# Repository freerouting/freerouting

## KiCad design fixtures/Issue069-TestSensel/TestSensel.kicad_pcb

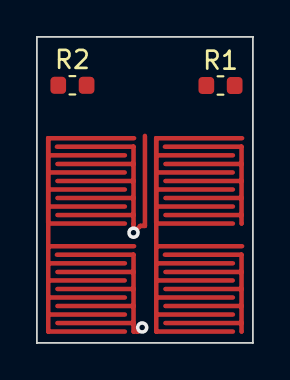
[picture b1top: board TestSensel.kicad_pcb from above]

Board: 2 copper layers, 12.0 x 17.0 mm, 6 parts (0 on the bottom side), 4 nets.

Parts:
J1, J2, J3, J4: Conn_01x02_Male; PCB_Fork_10mils_5mmx5mm
R1, R2: R_Small_US; R_0603_1608Metric

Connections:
/Col_1: J1.2, J2.2, R1.2
/Col_2: J3.2, J4.2, R1.1
/Row_1: J1.1, J3.1, R2.2
/Row_2: J2.1, J4.1, R2.1

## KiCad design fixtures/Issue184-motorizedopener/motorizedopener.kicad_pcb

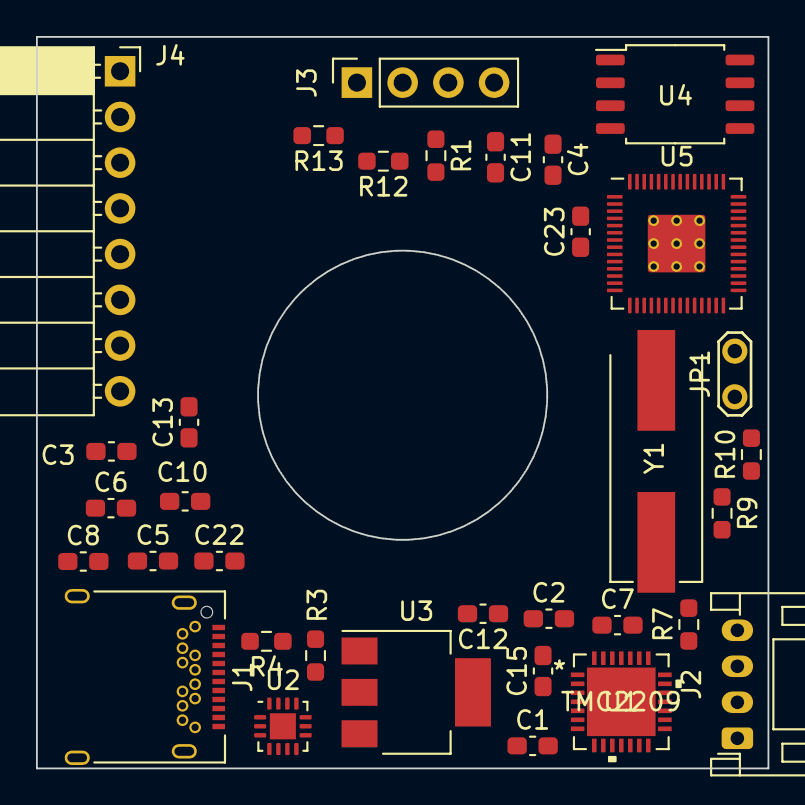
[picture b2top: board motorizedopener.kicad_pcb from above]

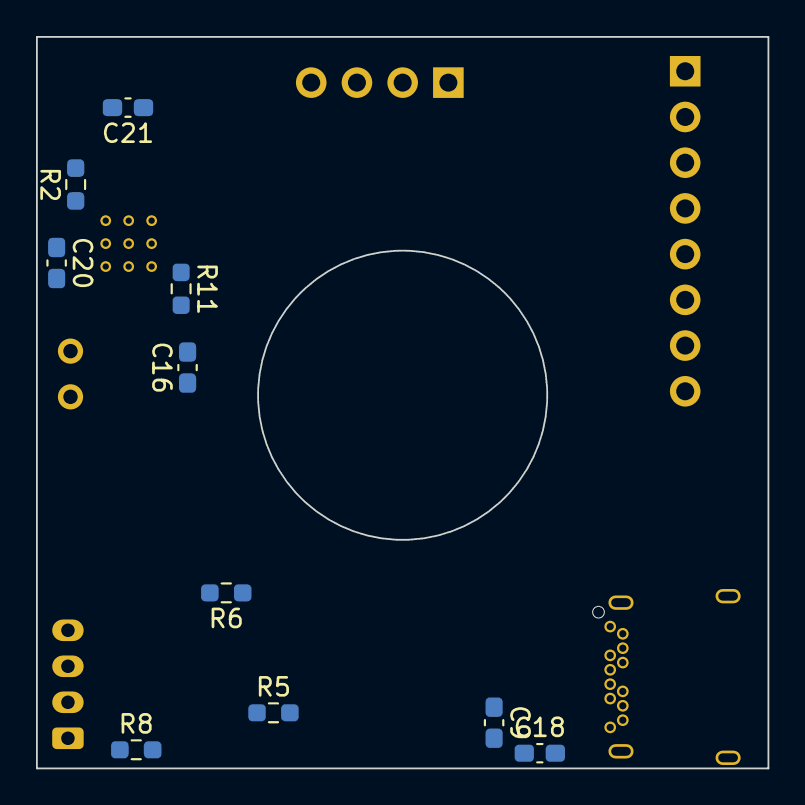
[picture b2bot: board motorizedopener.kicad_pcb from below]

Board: 2 copper layers, 40.6 x 40.6 mm, 44 parts (10 on the bottom side), 49 nets, no tracks yet.

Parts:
C1: 2.2uF; C_0603_1608Metric_Pad1.08x0.95mm_HandSolder
C2, C12: 22nF; C_0603_1608Metric_Pad1.08x0.95mm_HandSolder
C3, C21, C22: 1uF; C_0603_1608Metric_Pad1.08x0.95mm_HandSolder
C4, C6: 0.1uF; C_0603_1608Metric_Pad1.08x0.95mm_HandSolder
C5, C7, C11: 10uF; C_0603_1608Metric_Pad1.08x0.95mm_HandSolder
C8, C9: 470pF; C_0603_1608Metric_Pad1.08x0.95mm_HandSolder
C10, C18: 100nF; C_0603_1608Metric_Pad1.08x0.95mm_HandSolder
C13: 300nF; C_0603_1608Metric_Pad1.08x0.95mm_HandSolder
C15, C16: 27pF; C_0603_1608Metric_Pad1.08x0.95mm_HandSolder
C20: 200nF; C_0603_1608Metric_Pad1.08x0.95mm_HandSolder
C23: 700nF; C_0603_1608Metric_Pad1.08x0.95mm_HandSolder
J1: USB_C_Receptacle; USB_C_Receptacle_Amphenol_12401548E4-2A
J2: Stepper OUT; JST_PH_S4B-PH-K_1x04_P2.00mm_Horizontal
J3: I2C OLED; PinSocket_1x04_P2.54mm_Vertical
J4: SPI RFID; PinSocket_1x08_P2.54mm_Horizontal
JP1: Jumper_2_Open; TestPoint_2Pads_Pitch2.54mm_Drill0.8mm
R1, R7: 10k; R_0603_1608Metric_Pad0.98x0.95mm_HandSolder
R2, R3, R4: 4.7k; R_0603_1608Metric_Pad0.98x0.95mm_HandSolder
R5, R6: 220m; R_0603_1608Metric_Pad0.98x0.95mm_HandSolder
R8: 4.4k; R_0603_1608Metric_Pad0.98x0.95mm_HandSolder
R9, R10, R11: 1k; R_0603_1608Metric_Pad0.98x0.95mm_HandSolder
R12, R13: 27.4; R_0603_1608Metric_Pad0.98x0.95mm_HandSolder
U1: TMC2209
U2: FUSB302B01MPX; WQFN-14-1EP_2.5x2.5mm_P0.5mm_EP1.45x1.45mm
U3: NCP1117-3.3_SOT223; SOT-223-3_TabPin2
U4: W25Q128JVS; SOIC-8_5.23x5.23mm_P1.27mm
U5: RP2040; RP2040-QFN-56
Y1: 12.000MHZ; Crystal_SMD_HC49-US

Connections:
+1V1: C20.1, C21.2, U5.23 (DVDD), U5.45 (VREG_VOUT), U5.50 (DVDD)
+3V3: C3.2, C4.2, C10.1, C11.1, C18.1, C22.2, C23.1, J3.2, J4.1, R2.2, R3.2, R4.2, R7.2, U1.15 (VCC_IO), U2.3 (VDD), U2.4 (VDD), U3.2 (VO), U4.8 (VCC), U5.1 (IOVDD), U5.10 (IOVDD), U5.22 (IOVDD), U5.33 (IOVDD), U5.42 (IOVDD), U5.43 (ADC_AVDD), U5.44 (VREG_IN), U5.48 (USB_VDD), U5.49 (IOVDD)
GND: C1.2, C3.1, C4.1, C5.2, C6.2, C7.2, C8.2, C9.2, C10.2, C11.2, C13.2, C15.1, C16.1, C18.2, C20.2, C21.1, C22.1, C23.2, J1.A1 (GND), J1.A12 (GND), J1.B1 (GND), J1.B12 (GND), J1.S1 (SHIELD), J3.1, J4.3, JP1.1 (A), R1.1, R5.1, R6.1, R8.1, U1.3 (GND), U1.9 (MS1_AD0), U1.10 (MS2_AD1), U1.13 (CLK), U1.18 (GND), U1.20 (STDBY), U1.29 (GND), U2.8 (GND), U2.9 (GND), U2.15 (GND), U3.1 (GND), U4.4 (GND), U5.19 (TESTEN), U5.57 (GND)
unnamed: C1.1, U1.8 (5VOUT)
unnamed: C2.1, U1.4 (CPO)
unnamed: C2.2, U1.5 (CPI)
unnamed: C5.1, C6.1, U2.12 (VCONN), U2.13 (VCONN)
unnamed: C12.1, U1.6 (VCP)
unnamed: C15.2, U5.20 (XIN), Y1.1
unnamed: C16.2, R10.1, Y1.2
unnamed: J2.1, U1.26 (OB1)
unnamed: J2.2, U1.24 (OA1)
unnamed: J2.3, U1.21 (OA2)
unnamed: J2.4, U1.1 (OB2)
unnamed: J3.3, U5.30 (GPIO19)
unnamed: J3.4, U5.29 (GPIO18)
unnamed: J4.2, U5.9 (GPIO7)
unnamed: J4.4, U5.14 (GPIO11)
unnamed: J4.5, U5.15 (GPIO12)
unnamed: J4.6, U5.13 (GPIO10)
unnamed: J4.7, U5.16 (GPIO13)
unnamed: JP1.2 (B), R9.1
unnamed: R5.2, U1.23 (BRA)
unnamed: R6.2, U1.27 (BRB)
unnamed: R7.1, R8.2, U1.17 (VREF)
unnamed: R9.2, U4.1 (~CS), U5.56 (QSPI_SS)
unnamed: R10.2, U5.21 (XOUT)
unnamed: R11.1, U5.11 (GPIO8)
unnamed: R12.1, U5.47 (USB_DP)
unnamed: R13.1, U5.46 (USB_DM)
unnamed: U4.2 (DO(IO1)), U5.55 (QSPI_SD1)
unnamed: U4.3 (IO2), U5.54 (QSPI_SD2)
unnamed: U4.5 (DI(IO0)), U5.53 (QSPI_SD0)
unnamed: U4.6 (CLK), U5.52 (QSPI_SCLK)
unnamed: U4.7 (IO3), U5.51 (QSPI_SD3)
PWR-INT_N: R4.1, U2.5 (INT_N), U5.31 (GPIO20)
PWR-SCL: R3.1, U2.6 (SCL), U5.28 (GPIO17)
PWR-SDA: R2.1, U2.7 (SDA), U5.27 (GPIO16)
USB-D+: J1.A6 (D+), J1.B6 (D+), R12.2
USB-D-: J1.A7 (D-), J1.B7 (D-), R13.2
VBUS: C7.1, C12.2, C13.1, J1.A4 (VBUS), J1.A9 (VBUS), J1.B4 (VBUS), J1.B9 (VBUS), U1.22 (VS), U1.28 (VS), U2.2 (VBUS), U3.3 (VI)
cc1: C9.1, J1.A5 (CC1), U2.10 (CC1), U2.11 (CC1)
cc2: C8.1, J1.B5 (CC2), U2.1 (CC2), U2.14 (CC2)
tmc_DIAG: U1.11 (DIAG), U5.39 (GPIO27_ADC1)
tmc_DIR: U1.19 (DIR), U5.17 (GPIO14)
tmc_ENN: R1.2, U1.2 (ENN), U5.8 (GPIO6)
tmc_INDEX: U1.12 (INDEX), U5.38 (GPIO26_ADC0)
tmc_STEP: U1.16 (STEP), U5.18 (GPIO15)
tmc_UART: R11.2, U1.14 (PDN_UART), U5.12 (GPIO9)

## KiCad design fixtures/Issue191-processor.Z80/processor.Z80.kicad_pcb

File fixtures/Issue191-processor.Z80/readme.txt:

The processor.Z80 board is the central processor for the duodyne system.  It uses a Z80 8-bit CPU and includes dual-DMA channels.  It supports Interrupt Mode 2 (IM2) and an extended memory mapper.

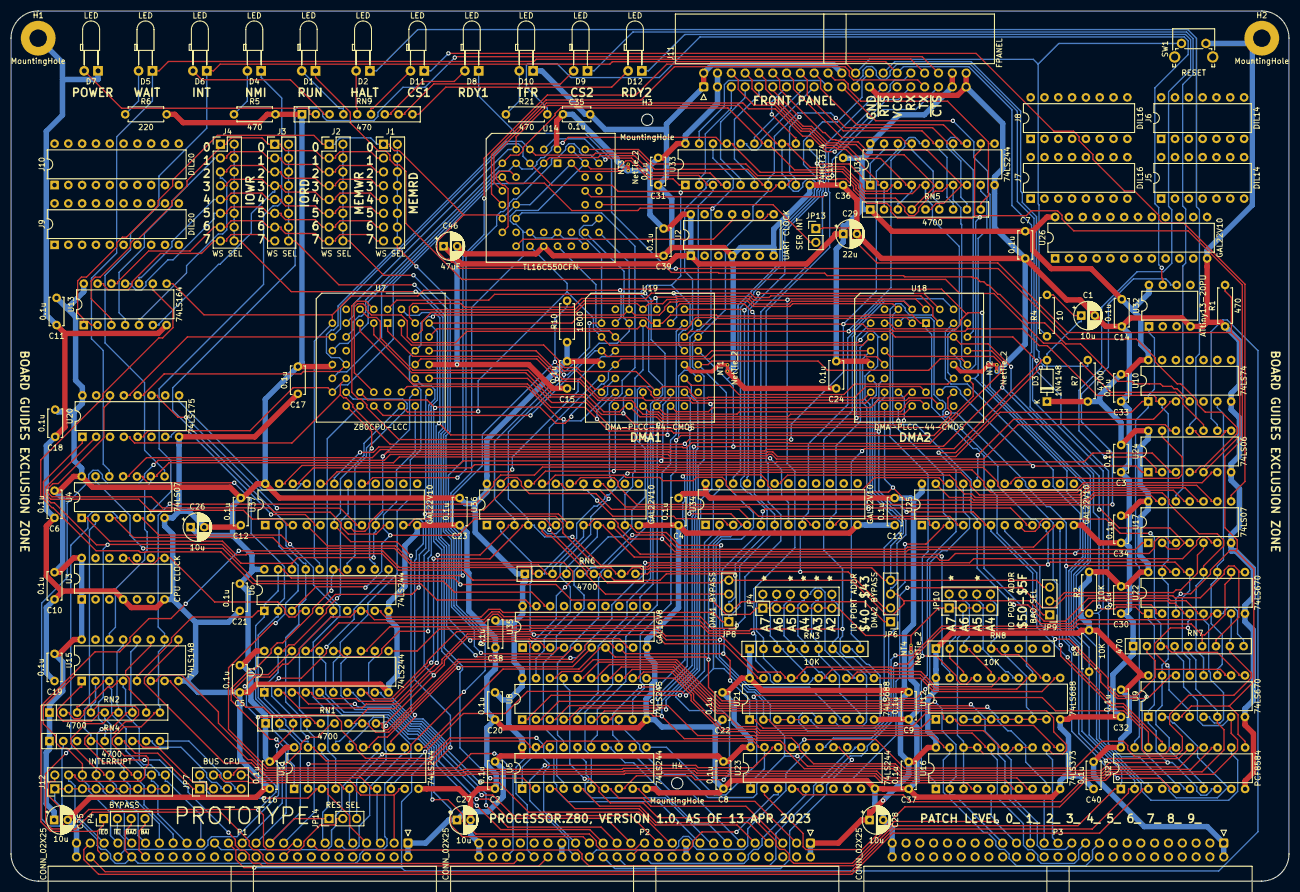
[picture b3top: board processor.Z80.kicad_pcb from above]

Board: 2 copper layers, 235.0 x 160.0 mm, 138 parts (0 on the bottom side), 244 nets.

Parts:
C1, C25, C26, C27, C28: 10u; CP_Radial_D5.0mm_P2.50mm
C2, C3, C4, C5, C6, C7, C8, C9, C10, C11, C12, C13, C14, C15, C16, C17, C18, C19, C20, C21, C22, C23, C24, C30, C31, C32, C33, C34, C35, C36, C37, C38, C39, C40: 0.1u; C_Disc_D5.0mm_W2.5mm_P5.00mm
C29: 22u; CP_Radial_D5.0mm_P2.50mm
C46: 47uF; CP_Radial_D5.0mm_P2.50mm
D1, D2, D4, D5, D6, D7, D8, D9, D10, D11, D12: LED; LED_D3.0mm_Horizontal_O3.81mm_Z2.0mm
D3: 1N4148; D_DO-35_SOD27_P7.62mm_Horizontal
H1, H2: MountingHole; MountingHole_3.2mm_M3_Pad
H3, H4: MountingHole; MountingHole_2.1mm
J1, J2, J3, J4: WS SEL; PinHeader_2x08_P2.54mm_Vertical
J5, J6: DIL14; DIP-14_W7.62mm
J7, J8: DIL16; DIP-16_W7.62mm
J9, J10: DIL20; DIP-20_W7.62mm
J11: FPANEL; IDC-Header_2x20_P2.54mm_Horizontal
J12: INTERRUPT; PinHeader_2x09_P2.54mm_Vertical
JP4: IO PORT ADDR; PinHeader_2x06_P2.54mm_Vertical
JP6: DMA2 BYPASS; PinHeader_1x04_P2.54mm_Vertical
JP7: BUS CPU; PinHeader_2x04_P2.54mm_Vertical
JP8: DMA1 BYPASS; PinHeader_1x04_P2.54mm_Vertical
JP9: BAO SEL; PinHeader_1x03_P2.54mm_Vertical
JP10: IO PORT ADDR; PinHeader_2x04_P2.54mm_Vertical
JP13: SER INT; PinHeader_1x02_P2.54mm_Vertical
JP14: RES SEL; PinHeader_1x03_P2.54mm_Vertical
NT1, NT2, NT3, NT4: NetTie_2; NetTie-2_THT_Pad0.3mm
P1, P2, P3: CONN_02X25; IDC-Header_2x25_P2.54mm_Horizontal
P4: BYPASS; PinHeader_1x04_P2.54mm_Vertical
R1, R5, R21: 470; R_Axial_DIN0207_L6.3mm_D2.5mm_P7.62mm_Horizontal
R2, R3: 10K; R_Axial_DIN0207_L6.3mm_D2.5mm_P7.62mm_Horizontal
R4: 10; R_Axial_DIN0207_L6.3mm_D2.5mm_P7.62mm_Horizontal
R6: 220; R_Axial_DIN0207_L6.3mm_D2.5mm_P7.62mm_Horizontal
R7: 4700; R_Axial_DIN0207_L6.3mm_D2.5mm_P7.62mm_Horizontal
R10: 1800; R_Axial_DIN0207_L6.3mm_D2.5mm_P7.62mm_Horizontal
RN1, RN2, RN4, RN5, RN6: 4700; R_Array_SIP9
RN3, RN8: 10K; R_Array_SIP9
RN7, RN9: 470; R_Array_SIP9
SW1: RESET; SW_Tactile_SPST_Angled_PTS645Vx58-2LFS
U1, U5, U6, U11, U23, U31: 74LS244; DIP-20_W7.62mm
U2: UART CLOCK; DIP-14_W7.62mm
U3: CPU CLOCK; DIP-14_W7.62mm
U4, U17: 74LS07; DIP-14_W7.62mm
U7: Z80CPU-LCC; PLCC-44_THT-Socket
U8: 74LS245; DIP-20_W7.62mm
U9, U22: 74LS670; DIP-16_W7.62mm
U10: 74LS74; DIP-14_W7.62mm
U12, U21: 74LS688; DIP-20_W7.62mm
U13: 74LS164; DIP-14_W7.62mm
U14: TL16C550CFN; PLCC-44_THT-Socket
U15: 74LS148; DIP-16_W7.62mm
U16: 74LS373; DIP-20_W7.62mm
U18, U19: DMA-PLCC-44-CMOS; PLCC-44_THT-Socket
U20: 74LS175; DIP-16_W7.62mm
U24: 74LS06; DIP-14_W7.62mm
U25, U26, U34, U36, U37: GAL22V10; DIP-24_W7.62mm
U27: PCF8584; DIP-20_W7.62mm
U32: ATtiny13-20PU; DIP-8_W7.62mm
U33: 74HCT374; DIP-20_W7.62mm
U35: GAL16V8; DIP-20_W7.62mm

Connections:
10KA: C1.1, D3.2 (A), R4.2, RN3.9 (R8), U4.11
470A: D7.2 (A), RN9.2 (R1)
470B: D6.2 (A), RN9.3 (R2)
470C: D1.2 (A), RN9.4 (R3)
470D: D2.2 (A), RN9.5 (R4)
470E: D11.2 (A), RN9.6 (R5)
470F: D8.2 (A), RN9.7 (R6)
470G: D9.2 (A), RN9.8 (R7)
470H: D12.2 (A), RN9.9 (R8)
+12V: P2.19, P2.20
-12V: P2.37, P2.38
/DMA/GND-DMA1: NT1.2, U19.34 (GND)
/DMA/GND-DMA2: NT2.2, U18.34 (GND)
/fpanel/FP-D0: J11.6, RN5.2 (R1), U31.2 (1A0)
/fpanel/FP-D1: J11.8, RN5.3 (R2), U31.4 (1A1)
/fpanel/FP-D2: J11.10, RN5.4 (R3), U31.6 (1A2)
/fpanel/FP-D3: J11.12, RN5.5 (R4), U31.8 (1A3)
/fpanel/FP-D4: J11.14, RN5.6 (R5), U31.17 (2A0)
/fpanel/FP-D5: J11.16, RN5.7 (R6), U31.15 (2A1)
/fpanel/FP-D6: J11.18, RN5.8 (R7), U31.13 (2A2)
/fpanel/FP-D7: J11.20, RN5.9 (R8), U31.11 (2A3)
/waitstate/1WS: J1.3, J2.3, J3.1, J4.1, U13.3 (Q0)
/waitstate/2WS: J1.5, J2.5, J3.3, J4.3, U13.4 (Q1)
/waitstate/3WS: J1.7, J2.7, J3.5, J4.5, U13.5 (Q2)
/waitstate/4WS: J1.9, J2.9, J3.7, J4.7, U13.6 (Q3)
/waitstate/5WS: J1.11, J2.11, J3.9, J4.9, U13.10 (Q4)
/waitstate/6WS: J1.13, J2.13, J3.11, J4.11, U13.11 (Q5)
/waitstate/7WS: J1.15, J2.15, J3.13, J4.13, U13.12 (Q6)
/waitstate/8WS: J3.15, J4.15, U13.13 (Q7)
A0: P2.35, U1.18 (1Y0)
A1: P2.33, U1.16 (1Y1)
A2: P2.31, U1.14 (1Y2)
A3: P2.29, U1.12 (1Y3)
A4: P2.27, U1.3 (2Y0)
A5: P2.25, U1.5 (2Y1)
A6: P2.23, U1.7 (2Y2)
A7: P2.21, U1.9 (2Y3)
A8: P2.17, U5.18 (1Y0)
A9: P2.15, U5.16 (1Y1)
A10: P2.13, U5.14 (1Y2)
A11: P2.11, U5.12 (1Y3)
A12: P2.9, U5.3 (2Y0)
A13: P2.7, U5.5 (2Y1)
A14: P2.5, U5.7 (2Y2)
A15: P2.3, U5.9 (2Y3)
A16: P2.36, U23.18 (1Y0)
A17: P2.34, U23.16 (1Y1)
A18: P2.32, U23.14 (1Y2)
A19: P2.30, U23.12 (1Y3)
A20: P2.28, U23.3 (2Y0)
A21: P2.26, U23.5 (2Y1)
BUSACK: U1.1 (1OE), U1.19 (2OE), U5.1 (1OE), U5.19 (2OE), U11.19 (2OE), U23.1 (1OE), U23.19 (2OE), U37.18 (O5)
CLK: P1.15, U6.16 (1Y1), U7.7 (CLK), U13.8 (CP), U18.8 (CLK), U19.8 (CLK), U27.1 (CLK)
CPU-A0: U1.2 (1A0), U7.34 (A0), U9.14 (Wa), U14.31 (A0), U18.7 (A0), U19.7 (A0), U22.14 (Wa), U27.6 (A0), U36.3 (I2)
CPU-A1: U1.4 (1A1), U7.35 (A1), U9.13 (Wb), U14.30 (A1), U18.5 (A1), U19.5 (A1), U22.13 (Wb), U25.10 (I9), U36.4 (I3)
CPU-A2: U1.6 (1A2), U7.36 (A2), U14.29 (A2), U18.4 (A2), U19.4 (A2), U21.6 (P2), U25.3 (I2)
CPU-A3: U1.8 (1A3), U7.37 (A3), U18.3 (A3), U19.3 (A3), U21.8 (P3), U36.11 (I10)
CPU-A4: U1.17 (2A0), U7.38 (A4), U12.11 (P4), U18.2 (A4), U19.2 (A4), U21.11 (P4)
CPU-A5: U1.15 (2A1), U7.39 (A5), U12.13 (P5), U18.1 (A5), U19.1 (A5), U21.13 (P5)
CPU-A6: U1.13 (2A2), U7.40 (A6), U12.15 (P6), U18.44 (A6), U19.44 (A6), U21.15 (P6)
CPU-A7: U1.11 (2A3), U7.41 (A7), U12.17 (P7), U18.43 (A7), U19.43 (A7), U21.17 (P7)
CPU-A8: U5.2 (1A0), U7.42 (A8), U18.26 (A8), U19.26 (A8)
CPU-A9: U5.4 (1A1), U7.43 (A9), U18.25 (A9), U19.25 (A9)
CPU-A10: U5.6 (1A2), U7.44 (A10), U18.24 (A10), U19.24 (A10)
CPU-A11: U5.8 (1A3), U7.1 (A11), U18.23 (A11), U19.23 (A11)
CPU-A12: U5.17 (2A0), U7.2 (A12), U18.22 (A12), U19.22 (A12)
CPU-A13: U5.15 (2A1), U7.3 (A13), U18.21 (A13), U19.21 (A13)
CPU-A14: U7.4 (A14), U9.5 (Ra), U18.20 (A14), U19.20 (A14), U22.5 (Ra), U25.5 (I4)
CPU-A15: U7.5 (A15), U9.4 (Rb), U18.19 (A15), U19.19 (A15), U22.4 (Rb), U25.6 (I5)
CPU-D0: U7.16 (D0), U8.2 (A0), U9.15 (D1), U10.2 (D), U14.2 (D0), U18.39 (D0), U19.39 (D0), U20.4 (D0), U22.15 (D1), U27.7 (D0), U31.18 (1Y0), U33.3 (D0)
CPU-D1: U7.17 (D1), U8.3 (A1), U9.1 (D2), U14.3 (D1), U18.38 (D1), U19.38 (D1), U20.5 (D1), U22.1 (D2), U27.8 (D1), U31.16 (1Y1), U33.4 (D1)
CPU-D2: U7.14 (D2), U8.4 (A2), U9.2 (D3), U14.4 (D2), U18.37 (D2), U19.37 (D2), U20.12 (D2), U22.2 (D3), U27.9 (D2), U31.14 (1Y2), U33.7 (D2)
CPU-D3: U7.9 (D3), U8.5 (A3), U9.3 (D4), U14.5 (D3), U18.36 (D3), U19.36 (D3), U20.13 (D3), U22.3 (D4), U27.11 (D3), U31.12 (1Y3), U33.8 (D3)
CPU-D4: U7.8 (D4), U8.6 (A4), U14.6 (D4), U18.35 (D4), U19.35 (D4), U27.12 (D4), U31.3 (2Y0), U33.13 (D4)
CPU-D5: U7.10 (D5), U8.7 (A5), U14.7 (D5), U18.32 (D5), U19.32 (D5), U27.13 (D5), U31.5 (2Y1), U33.14 (D5)
CPU-D6: U7.11 (D6), U8.8 (A6), U14.8 (D6), U18.33 (D6), U19.33 (D6), U27.14 (D6), U31.7 (2Y2), U33.17 (D6)
CPU-D7: U7.15 (D7), U8.9 (A7), U14.9 (D7), U18.31 (D7), U19.31 (D7), U27.15 (D7), U31.9 (2Y3), U33.18 (D7)
D0: P3.33, U8.18 (B0), U16.2 (O0)
D1: P3.31, U8.17 (B1), U16.5 (O1)
D2: P3.29, U8.16 (B2), U16.6 (O2)
D3: P3.27, U8.15 (B3), U16.9 (O3)
D4: P3.25, U8.14 (B4), U16.12 (O4)
D5: P3.23, U8.13 (B5), U16.15 (O5)
D6: P3.21, U8.12 (B6), U16.16 (O6)
D7: P3.19, U8.11 (B7), U16.19 (O7)
DATA-DIR: U8.1 (A->B), U34.23 (O0)
DATA_XFER: U32.6 (PB1), U36.18 (O5)
DMA-RDY1: U19.27 (RDY), U24.3, U37.23 (O0)
DMA-RDY2: U18.27 (RDY), U24.1, U37.22 (O1)
FP-LATCH-WR: U33.11 (Cp), U34.20 (O3)
GND: C1.2, C2.2, C3.2, C4.2, C5.2, C6.2, C7.2, C8.2, C9.2, C10.2, C11.2, C12.2, C13.2, C14.2, C15.2, C16.2, C17.2, C18.2, C19.2, C20.2, C21.2, C22.2, C23.2, C24.2, C25.2, C26.2, C27.2, C28.2, C29.2, C30.2, C31.2, C32.2, C33.2, C34.2, C35.2, C36.2, C37.2, C38.2, C39.2, C40.2, C46.2, D7.1 (K), D10.1 (K), H1.1, H2.1, J11.1, J11.2, J11.22, J11.25, J11.39, J11.40, NT1.1, NT2.1, NT4.1, P1.49, P1.50, P2.49, P2.50, P3.49, P3.50, R1.1, RN7.1 (common), SW1.2, U1.10 (GND), U2.4, U2.7, U3.4, U3.7, U4.7 (GND), U5.10 (GND), U6.10 (GND), U7.33 (GND), U8.10 (GND), U9.8 (GND), U10.7 (GND), U11.10 (GND), U12.10 (GND), U13.7 (GND), U14.22 (GND), U15.8 (GND), U16.10 (GND), U17.7 (GND), U20.8 (GND), U21.10 (GND), U22.8 (GND), U23.10 (GND), U24.7 (GND), U25.12 (GND), U26.12 (GND), U27.10 (VSS), U31.10 (GND), U32.4 (GND), U33.10 (GND), U34.12 (GND), U35.10 (GND), U36.12 (GND), U37.12 (GND)
I2C_SCL: J11.23, P1.47, R2.1, U27.3 (SCL)
I2C_SDA: J11.21, P1.48, R3.1, U27.2 (SDA)
INT: JP13.1 (A), R1.2, U24.5
INT-I2C: U24.13, U25.18 (O5)
IO-SEL: U34.3 (I2), U36.17 (O6)
unnamed: D1.1 (K), U24.10
unnamed: D2.1 (K), U24.8, U24.11
unnamed: D4.1 (K), U4.6
unnamed: D4.2 (A), R5.1
unnamed: D5.2 (A), R6.1
unnamed: D8.1 (K), U24.4
unnamed: D9.1 (K), U17.12
unnamed: D10.2 (A), R21.1
unnamed: D11.1 (K), U17.8
unnamed: D12.1 (K), U24.2
unnamed: J11.5, U33.2 (O0)
unnamed: J11.7, U33.5 (O1)
unnamed: J11.9, U33.6 (O2)
unnamed: J11.11, U33.9 (O3)
unnamed: J11.13, U33.12 (O4)
unnamed: J11.15, U33.15 (O5)
unnamed: J11.17, U33.16 (O6)
unnamed: J11.19, U33.19 (O7)
unnamed: J12.1, J12.3, J12.5, J12.7, J12.9, J12.11, J12.13, J12.15, J12.17, U24.12
unnamed: JP4.2, RN3.2 (R1), U21.18 (R7)
unnamed: JP4.4, RN3.3 (R2), U21.16 (R6)
unnamed: JP4.6, RN3.4 (R3), U21.14 (R5)
unnamed: JP4.8, RN3.5 (R4), U21.12 (R4)
unnamed: JP4.10, RN3.6 (R5), U21.9 (R3)
unnamed: JP4.12, RN3.7 (R6), U21.7 (R2)
unnamed: JP7.1, RN4.6 (R5)
unnamed: JP7.3, RN4.7 (R6)
unnamed: JP7.5, RN4.8 (R7)
unnamed: JP7.7, RN4.9 (R8)
unnamed: JP9.2, U17.5
unnamed: JP10.2, RN8.2 (R1), U12.18 (R7)
unnamed: JP10.4, RN8.3 (R2), U12.16 (R6)
unnamed: JP10.6, RN8.4 (R3), U12.14 (R5)
unnamed: JP10.8, RN8.5 (R4), U12.12 (R4)
unnamed: JP13.2 (B), U14.33 (INTR)
unnamed: R21.2, U32.7 (PB2)
unnamed: RN3.8 (R7), U21.3 (R0), U21.4 (P1), U21.5 (R1)
unnamed: RN8.6 (R5), U12.3 (R0), U12.4 (P1), U12.5 (R1), U12.6 (P2), U12.7 (R2), U12.8 (P3), U12.9 (R3)
unnamed: U14.10 (RCLK), U14.17 (~BAUDOUT)
unnamed: U15.6 (S2), U16.8 (D3)
unnamed: U15.7 (S1), U16.7 (D2)
unnamed: U15.9 (S0), U16.4 (D1)
ONE: J1.1, J2.1, NT3.2, U10.4 (~S), U13.1 (DSA), U13.2 (DSB), U14.14 (CS0), U14.15 (CS1), U14.43 (~RI)
RAW-CLK: U3.8, U3.11, U6.4 (1A1)
RDY_Q0: U20.2 (Q0), U37.3 (I2)
RDY_Q1: U20.7 (Q1), U37.5 (I4)
READY: U4.13, U35.18 (IO2)
RESET: U14.39 (MR), U37.17 (O6)
RX: J11.31, U14.11 (SIN)
SEL-A14: U5.13 (2A2), U25.22 (O1)
SEL-A15: U5.11 (2A3), U25.21 (O2)
TX: J11.33, U14.13 (SOUT)
UART-CLK: U2.8, U2.11, U14.18 (XIN)
VCC: C2.1, C3.1, C4.1, C5.1, C6.1, C7.1, C8.1, C9.1, C10.1, C11.1, C12.1, C13.1, C14.1, C15.1, C16.1, C17.1, C18.1, C19.1, C20.1, C21.1, C22.1, C23.1, C24.1, C25.1, C26.1, C27.1, C28.1, C29.1, C30.1, C31.1, C32.1, C33.1, C34.1, C35.1, C36.1, C37.1, C38.1, C39.1, C40.1, C46.1, D3.1 (K), J11.3, J11.4, J11.37, J11.38, NT3.1, P1.1, P1.2, P2.1, P2.2, P3.1, P3.2, R2.2, R3.2, R5.2, R6.2, R7.1, R10.1, RN1.1 (common), RN2.1 (common), RN3.1 (common), RN4.1 (common), RN5.1 (common), RN6.1 (common), RN8.1 (common), RN9.1 (common), U1.20 (VCC), U2.1, U2.14, U3.1, U3.14, U4.14 (VCC), U5.20 (VCC), U6.20 (VCC), U7.13 (+5V), U8.20 (VCC), U9.16 (VCC), U10.14 (VCC), U11.20 (VCC), U12.20 (VCC), U13.14 (VCC), U14.44 (VCC), U15.16 (VCC), U16.20 (VCC), U17.14 (VCC), U18.13 (VCC), U19.13 (VCC), U20.16 (VCC), U21.20 (VCC), U22.16 (VCC), U23.20 (VCC), U24.14 (VCC), U25.24 (VCC), U26.24 (VCC), U27.20 (VDD), U31.20 (VCC), U32.8 (VCC), U33.20 (VCC), U34.24 (VCC), U35.20 (VCC), U36.24 (VCC), U37.24 (VCC)
WS-IORD: J3.2, J3.4, J3.6, J3.8, J3.10, J3.12, J3.14, J3.16, U35.3 (I3)
WS-IOWR: J4.2, J4.4, J4.6, J4.8, J4.10, J4.12, J4.14, J4.16, U35.5 (I5)
WS-MEMRD: J1.2, J1.4, J1.6, J1.8, J1.10, J1.12, J1.14, J1.16, U35.2 (I2)
WS-MEMWR: J2.2, J2.4, J2.6, J2.8, J2.10, J2.12, J2.14, J2.16, U35.4 (I4)
ZERO: JP4.1, JP4.3, JP4.5, JP4.7, JP4.9, JP4.11, JP10.1, JP10.3, JP10.5, JP10.7, NT4.2, U6.1 (1OE), U6.19 (2OE), U11.1 (1OE), U14.21 (WR), U14.25 (RD), U14.28 (~ADS), U14.41 (~DSR), U14.42 (~DCD), U15.5 (EI), U16.3 (D0), U16.13 (D4), U16.14 (D5), U16.17 (D6), U16.18 (D7), U33.1 (OE)
mA14: RN7.2 (R1), U9.10 (Q1), U25.7 (I6)
mA15: RN7.3 (R2), U9.9 (Q2), U25.8 (I7)
mA16: RN7.4 (R3), U9.7 (Q3), U23.2 (1A0)
mA17: RN7.5 (R4), U9.6 (Q4), U23.4 (1A1)
mA18: RN7.6 (R5), U22.10 (Q1), U23.6 (1A2)
mA19: RN7.7 (R6), U22.9 (Q2), U23.8 (1A3)
mA20: RN7.8 (R7), U22.7 (Q3), U23.17 (2A0)
mA21: RN7.9 (R8), U22.6 (Q4), U23.15 (2A1)
~BAI: P1.40, P4.4
~BAO: P1.42, P4.3, RN1.9 (R8), RN4.2 (R1), U17.6
~BUS-EN: U8.19 (CE), U36.19 (O4)
~BUSACK: P1.13, U11.18 (1Y0)
~BUSRQ: P1.23, R10.2, U6.15 (2A1), U18.17 (~BUSREQ), U19.17 (~BUSREQ)
~CE_DMA_RDY: U36.22 (O1), U37.7 (I6)
~CPU-BUSACK: JP8.3, U7.27 (BUSACK), U19.16 (~BAI), U36.5 (I4)
~CPU-BUSRQ: U6.5 (2Y1), U7.29 (BUSRQ), U36.7 (I6)
~CPU-HALT: U7.20 (HALT), U11.4 (1A1)
~CPU-INT: U6.12 (1Y3), U7.18 (INT)
~CPU-IORQ: RN1.8 (R7), U7.22 (IOREQ), U11.17 (2A0), U12.1 (G), U18.11 (~IORQ), U19.11 (~IORQ), U21.1 (G), U25.9 (I8), U34.5 (I4), U35.8 (I8)
~CPU-M1: U7.31 (M1), U11.8 (1A3), U12.2 (P0), U16.11 (LE), U18.30 (~M1), U19.30 (~M1), U21.2 (P0), U34.4 (I3)
~CPU-MREQ: U7.21 (MREQ), U11.15 (2A1), U18.14 (~MREQ), U19.14 (~MREQ), U35.6 (I6)
~CPU-NMI: U6.14 (1Y2), U7.19 (NMI)
~CPU-RD: U7.23 (RD), U11.11 (2A3), U14.24 (~RD), U18.10 (~RD), U19.10 (~RD), U27.16 (~RD), U34.2 (I1), U35.7 (I7)
~CPU-RESET: RN4.5 (R4), U6.18 (1Y0), U7.30 (RESET), U10.1 (~R), U20.1 (~Mr), U27.19 (~RST), U32.1 (~RESET/PB5), U37.9 (I8)
~CPU-RFSH: U7.32 (RFSH), U11.6 (1A2), U35.9 (I9)
~CPU-WAIT: U6.3 (2Y0), U7.28 (WAIT), U36.6 (I5)
~CPU-WR: U7.26 (WR), U11.13 (2A2), U14.20 (~WR), U18.9 (~WR), U19.9 (~WR), U25.2 (I1), U34.10 (I9), U37.6 (I5)
~CS_I2C_WR: U25.17 (O6), U27.18 (~WR)
~CS_I2C: U25.19 (O4), U27.17 (~CS)
~CS_IO: U12.19 (P=R), U36.10 (I9)
~CS_MAP: U25.4 (I3), U36.16 (O7)
~CS_UART: U14.16 (~CS2), U36.15 (O8)
~CTS: J11.35, U14.40 (~CTS)
~DMA-ADDR: RN1.7 (R6), U21.19 (P=R), U36.2 (I1)
~DMA-BAO1: JP6.3, JP8.4, JP9.1, RN6.6 (R5), U18.16 (~BAI), U19.15 (~BA0)
~DMA-BAO2: JP6.4, JP9.3, RN6.8 (R7), U11.2 (1A0), U18.15 (~BA0), U37.11 (I10)
~DMA-CS1: U17.9, U19.18 (~CE/WAIT), U36.21 (O2)
~DMA-CS2: U17.13, U18.18 (~CE/WAIT), U36.20 (O3)
~DMA-IEI1: JP8.1, U6.9 (2Y3), U19.42 (IEI), U34.6 (I5)
~DMA-IEO1: JP6.1, JP8.2, RN6.7 (R6), U18.42 (IEI), U19.40 (IEO)
~DMA-IEO2: JP6.2, RN6.9 (R8), U18.40 (IEO), U34.8 (I7)
~DMA-INT-PULSE1: RN6.3 (R2), U4.3, U17.1, U19.41 (~INT/PULSE), U36.8 (I7)
~DMA-INT-PULSE2: RN6.4 (R3), U4.1, U17.3, U18.41 (~INT/PULSE), U36.9 (I8)
~DMA-RESET1: U19.12 (~RESET), U37.20 (O3)
~DMA-RESET2: U18.12 (~RESET), U37.19 (O4)
~DMA_RDY_WR: U20.9 (Cp), U37.21 (O2)
~DREQ0: P2.46, U37.2 (I1)
~DREQ1: P2.42, U37.4 (I3)
~EIRQ0: J12.4, P1.45, RN2.9 (R8), U15.10 (IO), U24.6
~EIRQ1: J12.6, P1.43, RN2.8 (R7), U15.11 (I1)
~EIRQ2: J12.8, P1.41, RN2.7 (R6), U15.12 (I2)
~EIRQ3: J12.10, P1.39, RN2.6 (R5), U15.13 (I3)
~EIRQ4: J12.12, P1.37, RN2.5 (R4), U15.1 (I4)
~EIRQ5: J12.14, P1.35, RN2.4 (R3), U15.2 (I5)
~EIRQ6: J12.16, P1.33, RN2.3 (R2), U15.3 (I6)
~EIRQ7: J12.18, P1.31, RN2.2 (R1), U15.4 (I7)
~EXT_RES: J11.24, JP14.3, R4.1, SW1.1
~FP-LATCH-RD: U31.1 (1OE), U31.19 (2OE), U34.21 (O2)
~FP-LATCH: U34.9 (I8), U36.23 (O0)
~HALT: P1.27, U11.16 (1Y1), U24.9
~IEI: P1.44, P4.2, RN1.3 (R2), U6.11 (2A3)
~IEO: P1.46, P4.1, RN6.2 (R1), U17.10
~IM2-EN-OE: J11.28, R7.2, U16.1 (OE)
~IM2-EN: J11.26, U34.22 (O1)
~IM2-IEO: U17.11, U34.19 (O4)
~IM2-INT: U4.9, U15.14 (GS), U34.7 (I6)
~INT0-EN: D6.1 (K), J11.30, U4.8, U17.2, U17.4
~INT0: J11.32, J12.2, P1.17, RN1.5 (R4), U6.8 (1A3)
~INT-I2C: RN6.5 (R4), U25.11 (I10), U27.5 (~INT)
~IORQ: JP7.2, P1.7, U11.3 (2Y0)
~M1: P1.11, U11.12 (1Y3)
~MREQ: JP7.4, P1.9, U11.5 (2Y1)
~MR: U13.9 (~MR), U35.19 (IO1)
~NMI: P1.19, RN1.4 (R3), U4.5, U6.6 (1A2)
~PAGE_EN: U9.11 (~Er), U10.6 (~Q), U22.11 (~Er)
~PAGE_WR: U9.12 (~Ew), U22.12 (~Ew), U25.23 (O0)
~PGEN_WR: U10.3 (C), U25.20 (O3)
~RD: JP7.8, P1.3, U11.9 (2Y3)
~RES_IN: JP14.2, P1.20
~RES_OUT: JP14.1, P1.21, RN1.2 (R1), U4.10, U6.2 (1A0)
~RFSH: P1.29, U11.14 (1Y2)
~RTS: J11.27, U14.36 (~RTS)
~TEND0: P2.44, RN4.3 (R2), U4.4
~TEND1: P2.40, RN4.4 (R3), U4.2
~USR-RESET1: U20.11 (~Q2), U37.8 (I7)
~USR-RESET2: U20.14 (~Q3), U37.10 (I9)
~WAIT-EN: D5.1 (K), J11.34, U4.12
~WAIT: J11.36, P1.25, RN1.6 (R5), U6.17 (2A0)
~WR: JP7.6, P1.5, U11.7 (2Y2)

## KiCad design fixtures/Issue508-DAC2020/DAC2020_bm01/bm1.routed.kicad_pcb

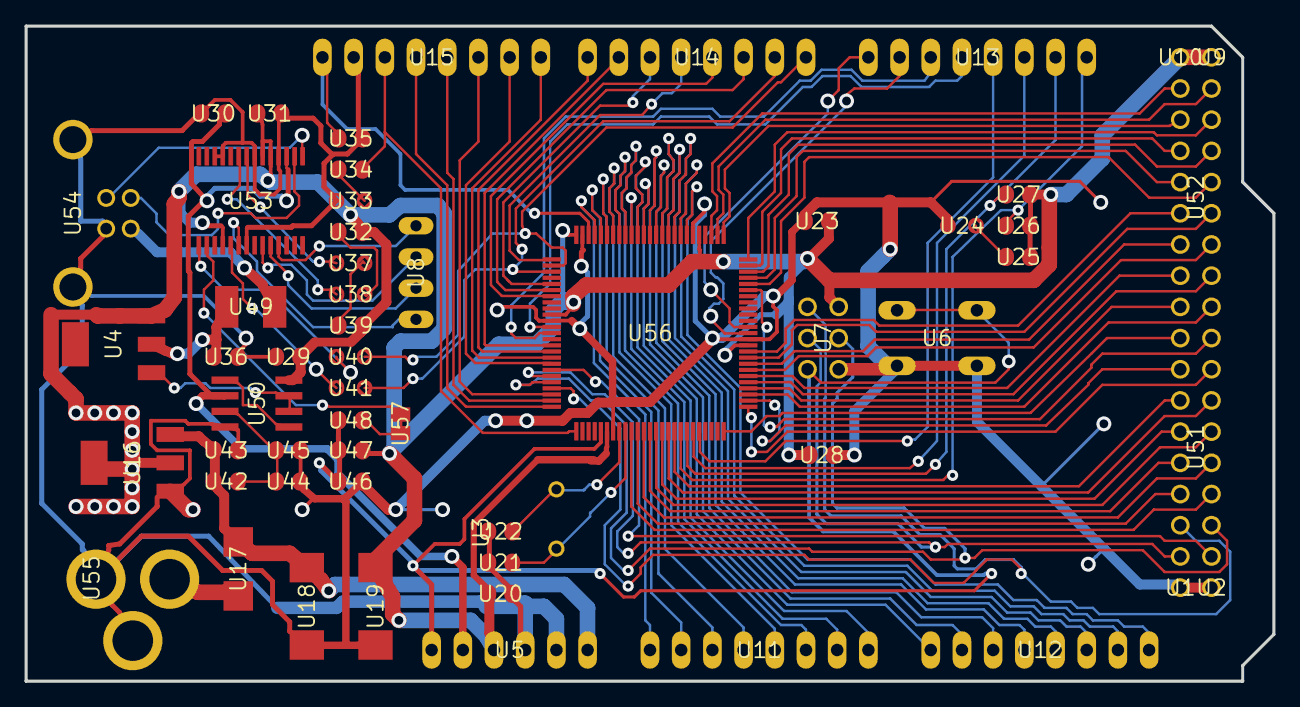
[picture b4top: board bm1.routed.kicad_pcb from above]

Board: 2 copper layers, 101.6 x 53.3 mm, 57 parts (0 on the bottom side), 99 nets.

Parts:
U1, U2, U9, U10: 1X01
U3: HC49_S
U4, U16: SOT223
U5: 1X06
U6: B3F-10XX
U7: 2X03
U8: JP4
U11, U12, U13, U14, U15: 1X08
U17: SMB
U18, U19: SMC_D
U20, U21, U22, U23, U28, U29, U30, U31, U35, U36, U43, U44, U46, U48: C0805RND
U24, U33, U37, U38: 0805RND
U25, U26, U27, U32, U34, U39, U42, U45, U47: R0805RND
U40, U41: RCL_0805RND
U49: L1812
U50: SO08
U51, U52: 2X08
U53: SSOP28
U54: PN61729
U55: DC-21MM
U56: TQFP100
U57: SJ

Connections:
+3V3: U5.2, U30.2, U50.2, U53.17
+5V: U4.3, U5.3, U7.2, U9.1, U10.1, U16.2, U16.4, U19.+, U20.1, U23.1, U25.1, U26.1, U27.1, U28.1, U29.2, U31.1, U32.2, U39.2, U47.2, U50.8, U53.4, U53.19, U53.20, U56.10, U56.31, U56.61, U56.80, U56.100
ADC0: U11.1, U56.97
ADC1: U11.2, U56.96
ADC2: U11.3, U56.95
ADC3: U11.4, U56.94
ADC4: U11.5, U56.93
ADC5: U11.6, U56.92
ADC6: U11.7, U56.91
ADC7: U11.8, U56.90
ADC8: U12.1, U56.89
ADC9: U12.2, U56.88
ADC10: U12.3, U56.87
ADC11: U12.4, U56.86
ADC12: U12.5, U56.85
ADC13: U12.6, U56.84
ADC14: U12.7, U56.83
ADC15: U12.8, U56.82
AREF: U15.8, U35.1, U56.98
CMP: U42.1, U44.2, U45.2, U50.3
CTS: U8.1, U53.11
D+: U53.15, U54.3
D-: U53.16, U54.2
DCD: U8.3, U53.10
DSR: U8.2, U53.9
DTR: U48.1, U53.2, U57.1, U57.2
GATE_CMD: U4.1, U50.6, U50.7
GND: U1.1, U2.1, U5.4, U5.5, U6.1, U6.2, U7.6, U15.7, U16.1, U18.-, U19.-, U20.2, U21.1, U22.1, U23.2, U24.P$2, U28.2, U29.1, U30.1, U31.2, U33.P$2, U35.2, U36.2, U43.2, U44.1, U45.1, U46.2, U50.4, U53.7, U53.18, U53.21, U53.25, U53.26, U54.4, U54.P$1, U54.P$2, U55.1, U55.3, U56.11, U56.32, U56.62, U56.81, U56.99
M8RXD: U40.P$1, U53.1
M8TXD: U41.P$1, U53.5
unnamed: U33.P$1, U34.2
unnamed: U24.P$1, U25.2
unnamed: U50.1, U50.5
unnamed: U3.1, U21.2, U56.34
unnamed: U3.2, U22.2, U56.33
unnamed: U38.P$2, U53.23
unnamed: U37.P$2, U53.22
unnamed: U32.1, U38.P$1
unnamed: U37.P$1, U39.1
unnamed: U49.2, U54.1
PA0: U52.16, U56.78
PA1: U52.15, U56.77
PA2: U52.14, U56.76
PA3: U52.13, U56.75
PA4: U52.12, U56.74
PA5: U52.11, U56.73
PA6: U52.10, U56.72
PA7: U52.9, U56.71
PB0: U51.1, U56.19
PB1: U7.3, U51.2, U56.20
PB2: U7.4, U51.3, U56.21
PB3: U7.1, U51.4, U56.22
PB4: U15.3, U56.23
PB5: U15.4, U56.24
PB6: U15.5, U56.25
PB7: U15.6, U34.1, U56.26
PC0: U52.1, U56.53
PC1: U52.2, U56.54
PC2: U52.3, U56.55
PC3: U52.4, U56.56
PC4: U52.5, U56.57
PC5: U52.6, U56.58
PC6: U52.7, U56.59
PC7: U52.8, U56.60
PD7: U51.16, U56.50
PE0: U14.1, U40.P$2, U56.2
PE1: U14.2, U41.P$2, U56.3
PE3: U14.6, U56.5
PE4: U14.3, U56.6
PE5: U14.4, U56.7
PG0: U51.13, U56.51
PG1: U51.14, U56.52
PG2: U51.15, U56.70
PG5: U14.5, U56.1
PH3: U14.7, U56.15
PH4: U14.8, U56.16
PH5: U15.1, U56.17
PH6: U15.2, U56.18
PL0: U51.5, U56.35
PL1: U51.6, U56.36
PL2: U51.7, U56.37
PL3: U51.8, U56.38
PL4: U51.9, U56.39
PL5: U51.10, U56.40
PL6: U51.11, U56.41
PL7: U51.12, U56.42
PWRIN: U17.A, U55.2
RESET: U5.1, U6.3, U6.4, U7.5, U46.1, U47.1, U48.2, U56.30
RI: U8.4, U53.6
RXD1: U13.3, U56.45
RXD2: U13.5, U56.12
RXD3: U13.7, U56.63
SCL: U13.1, U26.2, U56.43
SDA: U13.2, U27.2, U56.44
TXD1: U13.4, U56.46
TXD2: U13.6, U56.13
TXD3: U13.8, U56.64
USBVCC: U4.2, U36.1, U49.1
VIN: U5.6, U16.3, U17.C, U18.+, U42.2, U43.1

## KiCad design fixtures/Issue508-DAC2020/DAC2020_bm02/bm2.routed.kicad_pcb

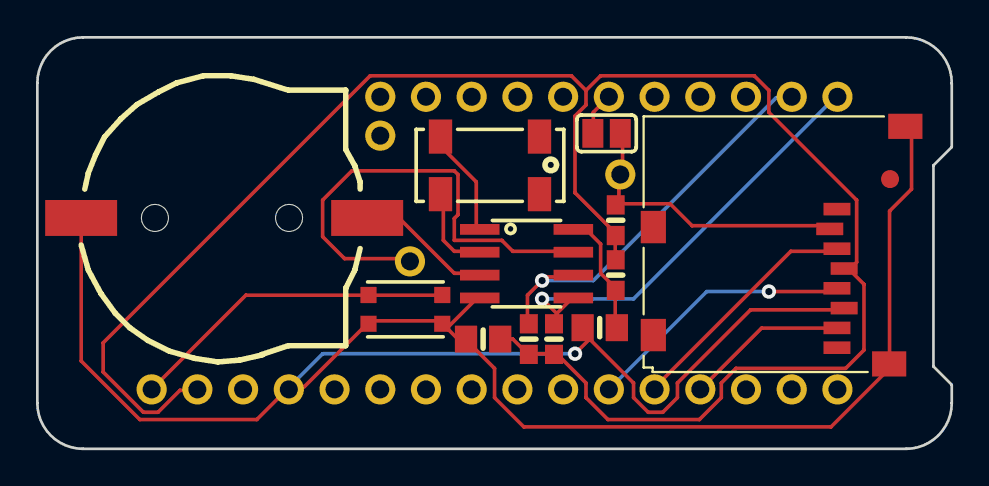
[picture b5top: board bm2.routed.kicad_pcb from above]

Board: 2 copper layers, 50.8 x 22.9 mm, 18 parts (0 on the bottom side), 15 nets.

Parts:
B1: cr1220; CR1220-2
C1, C2: 10uF; 0805-NO
FID1: FIDUCIAL_1MM
IC1: PCF8523T; SOIC8_150MIL
INT1: 1X01_ROUND
JP1: 1X11_ROUND
JP2: 1X16_ROUND
JP3: 1X01_ROUND
R1, R2: 10K; 0603-NO
R3: 100K; 0603-NO
R4: 1K; 0603-NO
SDCS: 1X01_ROUND
SJ1: SOLDERJUMPER_CLOSEDWIRE
SW1: KMR2; BTN_KMR2_4.6X2.8
X4: microsd; MICROSD
Y1: 32khz; CRYSTAL_8X3.8

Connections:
+3V3: C2.1, JP2.15, R1.2, R2.2, R3.2, R4.1, X4.4
CR1220: B1.+, IC1.3
CS: JP1.6, SJ1.1
GND: B1.-, C1.2, C2.2, IC1.4, JP2.13, SW1.A, SW1.A', X4.6, X4.MT1, X4.MT2
INT1: IC1.7, INT1.1
MISO: JP2.4, X4.7
MOSI: JP2.5, X4.3
unnamed: C1.1, IC1.8, R4.2
unnamed: IC1.1, Y1.P$4
unnamed: IC1.2, Y1.P$1
RESET: JP2.16, SW1.B, SW1.B'
SCK: JP2.6, X4.5
SCL: IC1.6, JP1.10, R2.1
SDA: IC1.5, JP1.11, R1.1
SD_CS: R3.1, SDCS.1, SJ1.2, X4.2

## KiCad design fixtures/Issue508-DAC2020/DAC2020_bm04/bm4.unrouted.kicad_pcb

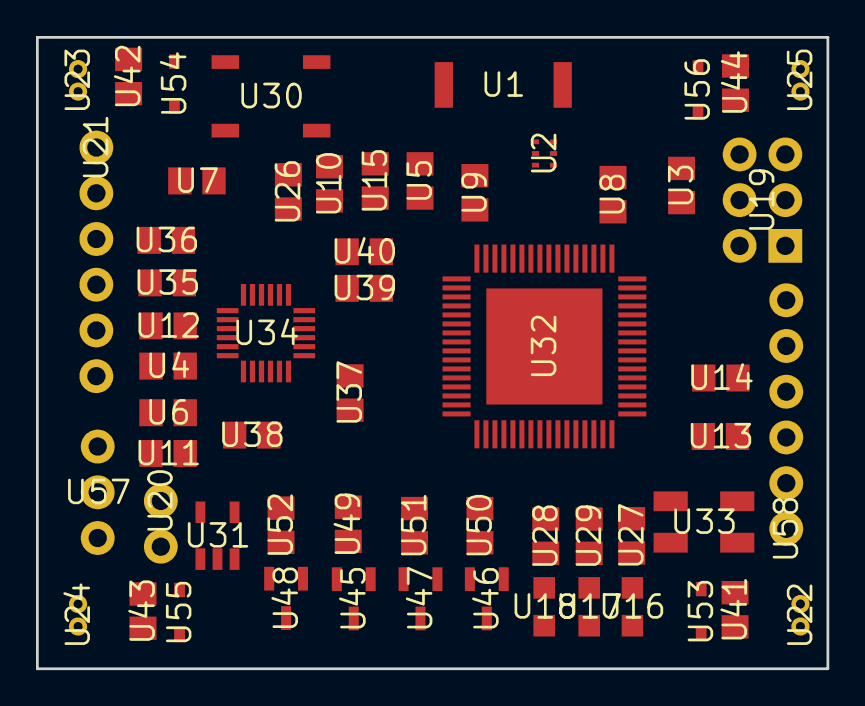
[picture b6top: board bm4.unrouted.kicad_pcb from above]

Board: 16 copper layers, 43.9 x 35.1 mm, 58 parts (0 on the bottom side), 44 nets, no tracks yet.

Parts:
U1: ANTENNA-CHIP5
U2: BALUN-0805
U3, U4, U5, U6, U7, U8, U9, U10, U11, U12, U13, U14, U15, U35, U36, U37, U38, U41, U42, U43, U44: C0805
U16, U17, U18: CHIP-LED0805
U19: 2X3-NS
U20: 1X02
U21, U58: FTDI_BASIC
U22, U23, U24, U25: 653002114822
U26, U27, U28, U29, U39, U40, U49, U50, U51, U52: R0805
U30: TACTILE_SWITCH_SMD
U31: SOT23-DBV
U32: QFN-64
U33: CRYSTAL-SMD-5X3
U34: LGA-24
U45, U46, U47, U48: CONTROLLER_SOT95P237X112-3N
U53, U54, U55, U56: SOD323_ST
U57: SWITCH-SPDT

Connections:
3.3V: U4.1, U12.1, U21.VCC, U26.2, U27.2, U31.5, U32.23, U32.34, U32.44, U32.54, U32.59, U34.15, U34.16, U34.17, U34.18, U35.1, U36.1, U39.2, U40.2, U58.VCC
/MISO: U19.1, U32.39
/MOSI: U19.4, U32.38
/PB4: U32.40, U47.1, U51.1
/PB5: U32.41, U46.1, U50.1
/PB6: U28.2, U32.42
/PB7: U29.2, U32.43
/PE3: U32.49, U48.1, U52.1
/PE4: U32.50, U45.1, U49.1
/RESET: U7.2, U19.5, U26.1, U30.1, U32.12
/RFANT: U1.FEED, U2.1, U15.2
/RX0: U21.TXO, U32.46
/RX1: U32.27, U58.TXO
/SCK: U19.3, U32.37
/SCL: U32.25, U34.21
/SDA: U32.26, U34.24
/TX0: U21.RXI, U32.47
/TX1: U32.28, U58.RXI
/VBAT: U11.1, U22.1, U23.1, U24.1, U25.1, U31.1, U31.3, U41.1, U42.1, U43.1, U44.1, U53.C, U54.C, U55.C, U56.C, U57.3
GND: U2.5, U3.2, U4.2, U5.2, U6.2, U10.2, U11.2, U12.2, U13.2, U14.2, U15.1, U16.C, U17.C, U18.C, U19.6, U20.1, U21.GND, U30.3, U31.2, U32.7, U32.10, U32.11, U32.20, U32.24, U32.33, U32.35, U32.45, U32.55, U32.58, U32.61, U32.65, U34.2, U34.3, U34.4, U34.5, U34.6, U34.22, U34.23, U35.2, U36.2, U38.1, U45.2, U46.2, U47.2, U48.2, U49.2, U50.2, U51.2, U52.2, U58.GND
unnamed: U18.A, U28.1
unnamed: U2.2, U5.1
unnamed: U2.3, U8.2
unnamed: U2.4, U9.1
unnamed: U17.A, U29.1
unnamed: U3.1, U32.60
unnamed: U10.1, U32.21, U32.22
unnamed: U13.1, U32.57, U33.3
unnamed: U14.1, U32.56, U33.1
unnamed: U22.2, U41.2, U47.3, U53.A
unnamed: U23.2, U42.2, U48.3, U54.A
unnamed: U6.1, U31.4
unnamed: U24.2, U43.2, U45.3, U55.A
unnamed: U25.2, U44.2, U46.3, U56.A
unnamed: U7.1, U21.DTR
unnamed: U8.1, U32.8
unnamed: U9.2, U32.9
unnamed: U34.9, U37.1
unnamed: U34.8, U37.2
unnamed: U34.7, U38.2
unnamed: U20.2, U57.2
unnamed: U16.A, U27.1
unnamed: U34.19, U39.1
unnamed: U34.20, U40.1

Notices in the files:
parts and their libraries:
Copyright 2021 Accelerated Designs. All rights reserved.
